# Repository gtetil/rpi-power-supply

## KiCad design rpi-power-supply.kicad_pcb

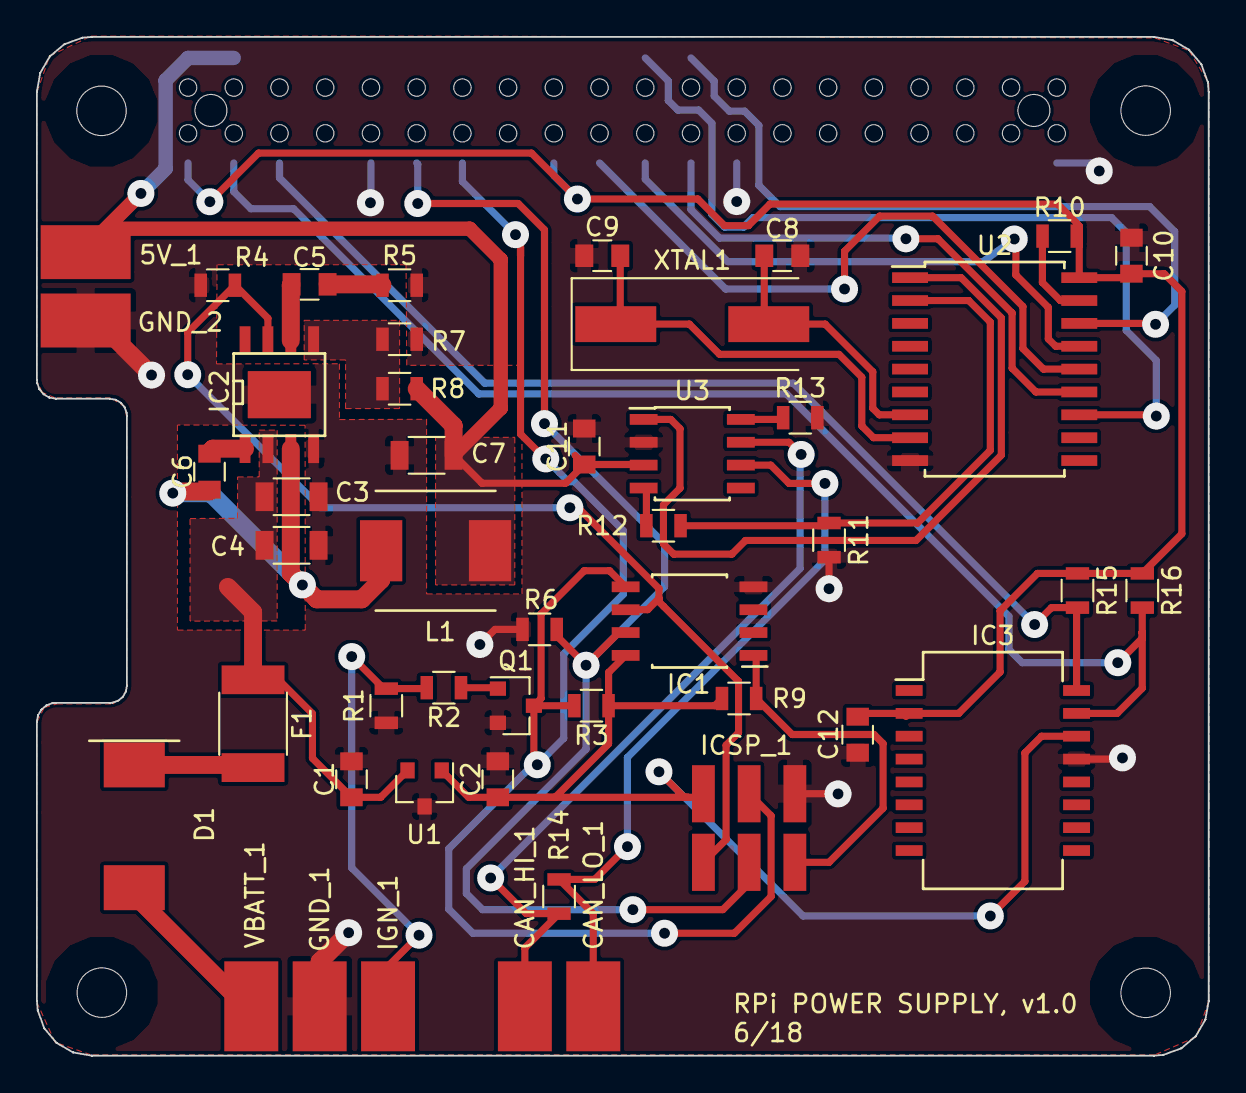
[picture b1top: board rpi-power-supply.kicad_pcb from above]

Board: 2 copper layers, 65.1 x 56.6 mm, 48 parts (1 on the bottom side), 34 nets.

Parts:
5V_1: CONN_01X01; 2mm_X_3mm_WIRE_PAD
C1, C2, C10, C11: 0.1uF; C_0805
C3, C4: 10uF; C_1206
C5: 3.9nF; C_0805
C6: 10nF; C_0805
C7: 33uF; C_1206
C8, C9: 22pF; C_0805
C12: 1uF; C_0805
CAN_HI_1: CONN_01X01; 2mm_X_3mm_WIRE_PAD
CAN_LO_1: CONN_01X01; 2mm_X_3mm_WIRE_PAD
CONN_1: Raspberry_Pi_2_3; 40-PIN_SMD_(M20-7812045)
D1: D_Schottky; DO-214AB
F1: Polyfuse; R_1812
GND_1, GND_2: CONN_01X01; 2mm_X_3mm_WIRE_PAD
IC1: ATTINY85-20SU; SOIC-8_WIDE_Pitch1.27mm
IC2: STEP_DOWN_CONVERTER_(MP2307); SOIC8N_(EXPOSED_PAD)
IC3: RTC_(DS3231); SOIC-16W_7.5x12.8mm_Pitch1.27mm
ICSP_1: CONN_02X03; 2X3_HEADER_SMD_HORIZONTAL
IGN_1: CONN_01X01; 2mm_X_3mm_WIRE_PAD
L1: 10uH; INDUCTOR_10uH_(ASPI-0630LR)
Q1: MOSFET_N_(2N7002P,215); SOT-23
R1, R3, R4, R6: 100k; R_0805
R2: 150; R_0805
R5: 6.8K; R_0805
R7: 2.2K; R_0805
R8: 10k; R_0805
R9: 1K; R_0805
R10, R12, R13, R15, R16: 10K; R_0805
R11: 22K; R_0805
R14: 120R; R_0805
U1: LM3480-3.3; SOT-23
U2: MCP2515T-I/SO; SOIC-18W_7.5x11.6mm_Pitch1.27mm
U3: MCP2551-I/SN; SOIC-8_3.9x4.9mm_Pitch1.27mm
VBATT_1: CONN_01X01; 2mm_X_3mm_WIRE_PAD
XTAL1: Crystal; Crystal_SMD_HC49-SD

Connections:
3.3V: C2.1, IC1.8, IC3.14, ICSP_1.2, R3.1, R9.1, U1.1
5V: 5V_1.1, C7.1, C11.1, CONN_1.2, CONN_1.4, L1.2, R8.1, U3.3
GND: C1.2, C2.2, C3.2, C4.2, C7.2, C8.2, C9.2, C10.2, C11.2, C12.2, CONN_1.6, CONN_1.9, CONN_1.14, CONN_1.20, CONN_1.25, CONN_1.30, CONN_1.34, CONN_1.39, GND_1.1, GND_2.1, IC1.4, IC2.4, IC2.9, IC3.13, ICSP_1.6, Q1.2, R1.2, R4.2, R5.2, R6.2, R7.2, R11.2, R13.2, U1.3, U2.9, U3.2
MISO: IC1.6, IC2.7, ICSP_1.1, R4.1
MOSI: CONN_1.13, IC1.5, ICSP_1.4, Q1.3, R3.2
unnamed: C1.1, C3.1, C4.1, F1.1, IC2.2, U1.2
unnamed: C5.1, IC2.6
unnamed: C5.2, R5.1
unnamed: C6.1, IC2.3, L1.1
unnamed: C6.2, IC2.1
unnamed: C8.1, U2.7, XTAL1.2
unnamed: C9.1, U2.8, XTAL1.1
unnamed: CAN_HI_1.1, R14.1, U3.7
unnamed: CAN_LO_1.1, R14.2, U3.6
unnamed: D1.1, F1.2
unnamed: D1.2, VBATT_1.1
unnamed: IC2.5, R7.1, R8.2
unnamed: IGN_1.1, R1.1, R2.2
unnamed: Q1.1, R2.1
unnamed: R10.2, U2.17
unnamed: R11.1, R12.2, U2.2
unnamed: R12.1, U3.4
unnamed: R13.1, U3.8
unnamed: U2.1, U3.1
PI_3.3V: C10.1, C12.1, CONN_1.1, CONN_1.17, IC3.2, R10.1, R15.1, R16.1, U2.18
PI_INT: CONN_1.22, U2.12
PI_MISO: CONN_1.21, U2.15
PI_MOSI: CONN_1.19, U2.14
PI_SCK: CONN_1.23, U2.13
PI_SCL: CONN_1.5, IC3.16, R15.2
PI_SDA: CONN_1.3, IC3.15, R16.2
PI_SS: CONN_1.24, U2.16
RST: IC1.1, ICSP_1.5, R9.2
SCK: CONN_1.11, IC1.7, ICSP_1.3, R6.1

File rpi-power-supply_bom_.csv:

Component,Description,Part,References,Value,Footprint,Quantity Per PCB,Datasheet
1,"Connector, single row, 01x01, pin header",CONN_01X01,"5V_1, CAN_HI_1, CAN_LO_1, GND_1, GND_2, IGN_1, VBATT_1",CONN_01X01,2mm_X_3mm_WIRE_PAD,7,
2,Unpolarized capacitor,C,"C1, C2, C10, C11",0.1uF,C_0805,4,
3,Unpolarized capacitor,C,C6,10nF,C_0805,1,
4,Unpolarized capacitor,C,"C3, C4",10uF,C_0805,2,
5,Unpolarized capacitor,C,C12,1uF,C_0805,1,
6,Unpolarized capacitor,C,"C8, C9",22pF,C_0805,2,
7,Unpolarized capacitor,C,C5,3.9nF,C_0805,1,
8,Unpolarized capacitor,C,C7,33uF,C_0805,1,
9,Schottky diode,D_Schottky,D1,D_Schottky,DO-214AB,1,
10,"resettable fuse, polymeric positive temperature coefficient (PPTC)",Polyfuse,F1,Polyfuse,R_1812,1,
11,"SO8 Wide, 2k Flash, 128B SRAM, 128B EEPROM, Debug Wire",ATTINY85-20SU,IC1,ATTINY85-20SU,SOIC-8_WIDE_Pitch1.27mm,1,http://www.atmel.com/images/atmel-2586-avr-8-bit-microcontro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
12,STEP_DOWN_CONVERTER_(MP2307),RTC_(DS3231),IC3,RTC_(DS3231),SOIC-16W_7.5x12.8mm_Pitch1.27mm,1,http://www.mouser.com/ds/2/277/MP2307_r1.9-371737.pdf
13,STEP_DOWN_CONVERTER_(MP2307),STEP_DOWN_CONVERTER_(MP2307),IC2,STEP_DOWN_CONVERTER_(MP2307),SOIC8N_(EXPOSED_PAD),1,http://www.mouser.com/ds/2/277/MP2307_r1.9-371737.pdf
14,"Connector, double row, 02x03, pin header",CONN_02X03,ICSP_1,CONN_02X03,Pin_Header_Straight_2x03_Pitch2.54mm_SMD,1,
15,expansion header for Raspberry Pi 2 & 3,Raspberry_Pi_2_3,J2,Raspberry_Pi_2_3,Pin_Header_Straight_2x20,1,https://www.raspberrypi.org/documentation/hardware/raspberry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
16,Inductor,L,L1,10uH,INDUCTOR_10uH_(ASPI-0630LR),1,
17,,"MOSFET_N_(2N7002P,215)",Q1,"MOSFET_N_(2N7002P,215)",SOT-23,1,
18,Resistor,R,"R1, R3, R4, R6",100k,R_0805,4,
19,Resistor,R,"R8, R10, R12, R13, R15, R16",10k,R_0805,6,
20,Resistor,R,R14,120R,R_0805,1,
21,Resistor,R,R2,150,R_0805,1,
22,Resistor,R,R9,1K,R_0805,1,
23,Resistor,R,R7,2.2K,R_0805,1,
24,Resistor,R,R11,22K,R_0805,1,
25,Resistor,R,R5,6.8K,R_0805,1,
26,"100mA, Quasi Low Dropout Voltage Regulator, 3.3V positive fixed output, SOT-23 package",LM3480-3.3,U1,LM3480-3.3,SOT-23,1,http://www.ti.com/lit/ds/symlink/lm3480.pdf
27,"Stand-Alone CAN Controller with SPI Interface, SOIC-18, Extended temperature range",MCP2515T-I/SO,U2,MCP2515T-I/SO,SOIC-18W_7.5x11.6mm_Pitch1.27mm,1,http://ww1.microchip.com/downloads/en/DeviceDoc/21801e.pdf
28,"High-Speed CAN Transceiver, 1Mbps, 5V supply, SOIC8 package",MCP2551-I/SN,U3,MCP2551-I/SN,SOIC-8_3.9x4.9mm_Pitch1.27mm,1,http://ww1.microchip.com/downloads/en/devicedoc/21667d.pdf
29,Two pin crystal,Crystal,Y1,Crystal,Crystal_SMD_HC49-SD,1,





Component Groups:,29
Component Count:,48
Fitted Components:,48
Number of PCBs:,1
Total components:,48
Schematic Version:,
Schematic Date:,
BoM Date:,4/16/2018 2:53:36 PM
Schematic Source:,C:\Users\gtetil\Documents\Projects\rpi-power-supply\rpi-power-supply.sch
KiCad Version:,Eeschema 4.0.6

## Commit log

2018-04-16 - Initial commit.
2018-04-16 - Finished schematic.
2018-04-17 - Started on PCB layout.
2018-04-20 - Finished PCB design.
2018-04-22 - Created LPKF files.
2018-04-22 - Missed the top isolate layer last time.
2018-06-08 - Added connection from ignition input to RPi input.
